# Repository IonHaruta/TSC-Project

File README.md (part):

# TSC - Project

## Diagrama bloc
Diagrama bloc a proiectului nostru prezintă conexiunile dintre senzorii folosiți, microcontrollerul ESP32-C6 și componentele auxiliare:

 <!-- imaginea se pune în folderul proiectului -->

## Prezentare generală

Acest proiect TSC constă într-un sistem integrat care monitorizează temperatura și umiditatea mediului înconjurător cu ajutorul unui senzor DHT22 și afișează datele în timp real pe un ecran OLED SSD1306. Controlul și logica sistemului sunt gestionate de microcontrollerul ESP32-C6, iar interacțiunea utilizatorului se face printr-un buton fizic. Toate componentele sunt alimentate prin USB și sunt integrate pe o placă PCB proiectată în Fusion 360.

## BOM (Bill Of Materials)

| Component       | Device                | Link                                                                 | Datasheet                                                                 |
|-----------------|-----------------------|----------------------------------------------------------------------|---------------------------------------------------------------------------|
| BOOT_BUTTON     | BUTTON_CUSYOMV1        | [Link](https://ro.mouser.com/ProductDetail/Panasonic/EVQ-P7L01P?qs=rJ%252BziJWpyszWhhNszc02jQ%3D%3D&_gl=1*xzqk3l*_ga*dW5kZWZpbmVk*_ga_15W4STQT4T*dW5kZWZpbmVk*_ga_1KQLCYKRX3*dW5kZWZpbmVk)     | [Datasheet](https://componentsearchengine.com/Datasheets/2/EVQP7L01P.pdf) |
| C1              | ESP32_WROVER_EAGLE-LTSPICE_CC0402 | [Link](https://ro.mouser.com/ProductDetail/YAGEO/CC0402MRX5R5BB106?qs=zEY9bCHj09eCmUJdZuS5Lg%3D%3D)  | [Datasheet](https://componentsearchengine.com/Datasheets/2/CC0402MRX5R5BB106.pdf) |
| C1_BAT          | ESP32_WROVER_EAGLE-LTSPICE_CC0402 | [Link](https://ro.mouser.com/ProductDetail/YAGEO/CC0402MRX5R5BB106?qs=zEY9bCHj09eCmUJdZuS5Lg%3D%3D)  | [Datasheet](https://componentsearchengine.com/Datasheets/2/CC0402MRX5R5BB106.pdf) |
| C1_BAT1         | EAGLE-LTSPICE_CC0402   | [Link](https://ro.mouser.com/ProductDetail/YAGEO/CC0402MRX5R5BB106?qs=zEY9bCHj09eCmUJdZuS5Lg%3D%3D)  | [Datasheet](https://componentsearchengine.com/Datasheets/2/CC0402MRX5R5BB106.pdf) |
| C1_BAT2         | EAGLE-LTSPICE_CC0402   | [Link](https://ro.mouser.com/ProductDetail/YAGEO/CC0402MRX5R5BB106?qs=zEY9bCHj09eCmUJdZuS5Lg%3D%3D)  | [Datasheet](https://componentsearchengine.com/Datasheets/2/CC0402MRX5R5BB106.pdf) |
| C2              | ESP32_WROVER_EAGLE-LTSPICE_CC0402 | [Link](https://ro.mouser.com/ProductDetail/YAGEO/CC0402MRX5R5BB106?qs=zEY9bCHj09eCmUJdZuS5Lg%3D%3D)  | [Datasheet](https://componentsearchengine.com/Datasheets/2/CC0402MRX5R5BB106.pdf) |
| C2_BAT          | ESP32_WROVER_EAGLE-LTSPICE_CC0402 | [Link](https://ro.mouser.com/ProductDetail/YAGEO/CC0402MRX5R5BB106?qs=zEY9bCHj09eCmUJdZuS5Lg%3D%3D)  | [Datasheet](https://componentsearchengine.com/Datasheets/2/CC0402MRX5R5BB106.pdf) |
| C3              | RCL_CPOL-EUCT3528      | [Link](https://ro.mouser.com/ProductDetail/YAGEO/CC0402MRX5R5BB106?qs=zEY9bCHj09eCmUJdZuS5Lg%3D%3D)  | [Datasheet](https://componentsearchengine.com/Datasheets/2/CC0402MRX5R5BB106.pdf) |
| C4              | ESP32_WROVER_EAGLE-LTSPICE_CC0402 | [Link](https://ro.mouser.com/ProductDetail/YAGEO/CC0402MRX5R5BB106?qs=zEY9bCHj09eCmUJdZuS5Lg%3D%3D)  | [Datasheet](https://componentsearchengine.com/Datasheets/2/CC0402MRX5R5BB106.pdf) |
| C4_USB          | ESP32_WROVER_EAGLE-LTSPICE_CC0402 | [Link](https://ro.mouser.com/ProductDetail/YAGEO/CC0402MRX5R5BB106?qs=zEY9bCHj09eCmUJdZuS5Lg%3D%3D)  | [Datasheet](https://componentsearchengine.com/Datasheets/2/CC0402MRX5R5BB106.pdf) |
| C5              | ESP32_WROVER_EAGLE-LTSPICE_CC0402 | [Link](https://ro.mouser.com/ProductDetail/YAGEO/CC0402MRX5R5BB106?qs=zEY9bCHj09eCmUJdZuS5Lg%3D%3D)  | [Datasheet](https://componentsearchengine.com/Datasheets/2/CC0402MRX5R5BB106.pdf) |
| C5_USB          | ESP32_WROVER_EAGLE-LTSPICE_CC0402 | [Link](https://ro.mouser.com/ProductDetail/YAGEO/CC0402MRX5R5BB106?qs=zEY9bCHj09eCmUJdZuS5Lg%3D%3D)  | [Datasheet](https://componentsearchengine.com/Datasheets/2/CC0402MRX5R5BB106.pdf) |
| C6              | ESP32_WROVER_EAGLE-LTSPICE_CC0402 | [Link](https://ro.mouser.com/ProductDetail/YAGEO/CC0402MRX5R5BB106?qs=zEY9bCHj09eCmUJdZuS5Lg%3D%3D)  | [Datasheet](https://componentsearchengine.com/Datasheets/2/CC0402MRX5R5BB106.pdf) |
| C7              | ESP32_WROVER_EAGLE-LTSPICE_CC0402 | [Link](https://ro.mouser.com/ProductDetail/YAGEO/CC0402MRX5R5BB106?qs=zEY9bCHj09eCmUJdZuS5Lg%3D%3D)  | [Datasheet](https://componentsearchengine.com/Datasheets/2/CC0402MRX5R5BB106.pdf) |
| C8              | ESP32_WROVER_EAGLE-LTSPICE_CC0402 | [Link](https://ro.mouser.com/ProductDetail/YAGEO/CC0402MRX5R5BB106?qs=zEY9bCHj09eCmUJdZuS5Lg%3D%3D)  | [Datasheet](https://componentsearchengine.com/Datasheets/2/CC0402MRX5R5BB106.pdf) |
| C9              | EAGLE-LTSPICE_CC0402   | [Link](https://ro.mouser.com/ProductDetail/YAGEO/CC0402MRX5R5BB106?qs=zEY9bCHj09eCmUJdZuS5Lg%3D%3D)  | [Datasheet](https://componentsearchengine.com/Datasheets/2/CC0402MRX5R5BB106.pdf) |
| C10             | ESP32_WROVER_EAGLE-LTSPICE_CC0402 | [Link](https://ro.mouser.com/ProductDetail/YAGEO/CC0402MRX5R5BB106?qs=zEY9bCHj09eCmUJdZuS5Lg%3D%3D)  | [Datasheet](https://componentsearchengine.com/Datasheets/2/CC0402MRX5R5BB106.pdf) |
| C10_SUPERCAP    | CPH3225A               | [Link](https://ro.mouser.com/ProductDetail/Seiko-Semiconductors/CPH3225A?qs=3etwrb1wR%252BhUOph6lAO7eg%3D%3D) | [Datasheet](https://ro.mouser.com/datasheet/2/360/Seiko_Instruments_MicroBattery_E_20230330_2024Jan_-3561061.pdf) |
| CHANGE_BUTTON   | BUTTON_CUSYOMV1        | [Link](https://ro.mouser.com/ProductDetail/Panasonic/EVQ-P7L01P?qs=rJ%252BziJWpyszWhhNszc02jQ%3D%3D&_gl=1*xzqk3l*_ga*dW5kZWZpbmVk*_ga_15W4STQT4T*dW5kZWZpbmVk*_ga_1KQLCYKRX3*dW5kZWZpbmVk)     | [Datasheet](https://componentsearchengine.com/Datasheets/2/EVQP7L01P.pdf) |
| C_DELAY         | ESP32_WROVER_EAGLE-LTSPICE_CC0402 | [Link](https://ro.mouser.com/ProductDetail/YAGEO/CC0402MRX5R5BB106?qs=zEY9bCHj09eCmUJdZuS5Lg%3D%3D)  | [Datasheet](https://componentsearchengine.com/Datasheets/2/CC0402MRX5R5BB106.pdf) |
| D1              | USBLC6-2SC6Y           | [Link](https://ro.mouser.com/ProductDetail/STMicroelectronics/USBLC6-2SC6Y?qs=gNDSiZmRJS%2FOgDexvXkdow%3D%3D) | [Datasheet](https://ro.mouser.com/datasheet/2/389/usblc6_2sc6y-1852505.pdf) |
| D2              | ESP32_WROVER_AVX...SD0805S020S1R0_AVX_... | [Link](https://eu.mouser.com/ProductDetail/KYOCERA-AVX/SD0805S020S1R0?qs=jCA%252BPfw4LHbpkAoSnwrdjw%3D%3D) | [Datasheet](http://datasheets.avx.com/schottky.pdf) |
| D3              | MBR0530               | [Link](https://www.snapeda.com/parts/MBR0530/Onsemi/view-part/?ref=eda) | [Datasheet](https://www.snapeda.com/parts/MBR0530/Onsemi/view-part/?ref=eda) |
| D4              | MBR0530               | [Link](https://www.snapeda.com/parts/MBR0530/Onsemi/view-part/?ref=eda) | [Datasheet](https://www.snapeda.com/parts/MBR0530/Onsemi/view-part/?ref=eda) |
| D5              | MBR0530               | [Link](https://www.snapeda.com/parts/MBR0530/Onsemi/view-part/?ref=eda) | [Datasheet](https://www.snapeda.com/parts/MBR0530/Onsemi/view-part/?ref=eda) |
| D6              | PGB1010603MR          | [Link](https://www.snapeda.com/parts/PGB1010603MR/Littelfuse/view-part/?ref=eda) | [Datasheet](https://www.snapeda.com/parts/PGB1010603MR/Littelfuse/view-part/?ref=eda) |
| D7              | ESP32_WROVER_AVX---SD0805S020S1R0_AVX_... | [Link](https://eu.mouser.com/ProductDetail/KYOCERA-AVX/SD0805S020S1R0?qs=jCA%252BPfw4LHbpkAoSnwrdjw%3D%3D) | [Datasheet](http://datasheets.avx.com/schottky.pdf) |
| D8              | PGB1010603MR          | [Link](https://www.snapeda.com/parts/PGB1010603MR/Littelfuse/view-part/?ref=eda) | [Datasheet](https://www.snapeda.com/parts/PGB1010603MR/Littelfuse/view-part/?ref=eda) |
| D9              | PGB1010603MR          | [Link](https://www.snapeda.com/parts/PGB1010603MR/Littelfuse/view-part/?ref=eda) | [Datasheet](https://www.snapeda.com/parts/PGB1010603MR/Littelfuse/view-part/?ref=eda) |
| D10             | PGB1010603MR          | [Link](https://www.snapeda.com/parts/PGB1010603MR/Littelfuse/view-part/?ref=eda) | [Datasheet](https://www.snapeda.com/parts/PGB1010603MR/Littelfuse/view-part/?ref=eda) |
| D11             | PGB1010603MR          | [Link](https://www.snapeda.com/parts/PGB1010603MR/Littelfuse/view-part/?ref=eda) | [Datasheet](https://www.snapeda.com/parts/PGB1010603MR/Littelfuse/view-part/?ref=eda) |
| D12             | PGB1010603MR          | [Link](https://www.snapeda.com/parts/PGB1010603MR/Littelfuse/view-part/?ref=eda) | [Datasheet](https://www.snapeda.com/parts/PGB1010603MR/Littelfuse/view-part/?ref=eda) |
| EPD_C1          | ESP32_WROVER_EAGLE-LTSPICE_CC0402 | [Link](https://ro.mouser.com/ProductDetail/YAGEO/CC0402MRX5R5BB106?qs=zEY9bCHj09eCmUJdZuS5Lg%3D%3D)  | [Datasheet](https://componentsearchengine.com/Datasheets/2/CC0402MRX5R5BB106.pdf) |
| EPD_C2          | ESP32_WROVER_EAGLE-LTSPICE_CC0402 | [Link](https://ro.mouser.com/ProductDetail/YAGEO/CC0402MRX5R5BB106?qs=zEY9bCHj09eCmUJdZuS5Lg%3D%3D)  | [Datasheet](https://componentsearchengine.com/Datasheets/2/CC0402MRX5R5BB106.pdf) |
| EPD_C5          | ESP32_WROVER_EAGLE-LTSPICE_CC0402 | [Link](https://ro.mouser.com/ProductDetail/YAGEO/CC0402MRX5R5BB106?qs=zEY9bCHj09eCmUJdZuS5Lg%3D%3D)  | [Datasheet](https://componentsearchengine.com/Datasheets/2/CC0402MRX5R5BB106.pdf) |
| EPD_C6          | ESP32_WROVER_EAGLE-LTSPICE_CC0402 | [Link](https://ro.mouser.com/ProductDetail/YAGEO/CC0402MRX5R5BB106?qs=zEY9bCHj09eCmUJdZuS5Lg%3D%3D)  | [Datasheet](https://componentsearchengine.com/Datasheets/2/CC0402MRX5R5BB106.pdf) |
| EPD_C7          | ESP32_WROVER_EAGLE-LTSPICE_CC0402 | [Link](https://ro.mouser.com/ProductDetail/YAGEO/CC0402MRX5R5BB106?qs=zEY9bCHj09eCmUJdZuS5Lg%3D%3D)  | [Datasheet](https://componentsearchengine.com/Datasheets/2/CC0402MRX5R5BB106.pdf) |
| EPD_C8          | ESP32_WROVER_EAGLE-LTSPICE_CC0402 | [Link](https://ro.mouser.com/ProductDetail/YAGEO/CC0402MRX5R5BB106?qs=zEY9bCHj09eCmUJdZuS5Lg%3D%3D)  | [Datasheet](https://componentsearchengine.com/Datasheets/2/CC0402MRX5R5BB106.pdf) |
| EPD_C9          | ESP32_WROVER_EAGLE-LTSPICE_CC0402 | [Link](https://ro.mouser.com/ProductDetail/YAGEO/CC0402MRX5R5BB106?qs=zEY9bCHj09eCmUJdZuS5Lg%3D%3D)  | [Datasheet](https://componentsearchengine.com/Datasheets/2/CC0402MRX5R5BB106.pdf) |
| EPD_C10         | ESP32_WROVER_EAGLE-LTSPICE_CC0402 | [Link](https://ro.mouser.com/ProductDetail/YAGEO/CC0402MRX5R5BB106?qs=zEY9bCHj09eCmUJdZuS5Lg%3D%3D)  | [Datasheet](https://componentsearchengine.com/Datasheets/2/CC0402MRX5R5BB106.pdf) |
| EPD_C11         | ESP32_WROVER_EAGLE-LTSPICE_CC0402 | [Link](https://ro.mouser.com/ProductDetail/YAGEO/CC0402MRX5R5BB106?qs=zEY9bCHj09eCmUJdZuS5Lg%3D%3D)  | [Datasheet](https://componentsearchengine.com/Datasheets/2/CC0402MRX5R5BB106.pdf) |
| EPD_C12         | ESP32_WROVER_EAGLE-LTSPICE_CC0402 | [Link](https://ro.mouser.com/ProductDetail/YAGEO/CC0402MRX5R5BB106?qs=zEY9bCHj09eCmUJdZuS5Lg%3D%3D)  | [Datasheet](https://componentsearchengine.com/Datasheets/2/CC0402MRX5R5BB106.pdf) |
| IC1             | BD5229G-TR            | [Link](https://ro.mouser.com/ProductDetail/ROHM-Semiconductor/BD5229G-TR?qs=4kLU8WoGk0vvnhrrYwdszw%3D%3D) | [Datasheet](https://fscdn.rohm.com/en/products/databook/datasheet/ic/power/voltage_detector/bd52xxg-e.pdf) |
| IC4             | XC6220A331MR-G        | [Link](https://ro.mouser.com/ProductDetail/Torex-Semiconductor/XC6220A331MR-G?qs=AsjdqWjXhJ8ZSWznL1J0gg%3D%3D) | [Datasheet](https://ro.mouser.com/datasheet/2/760/xc6220-3371556.pdf) |
| J1              | FH34SRJ-24S-0.5SH_99_ | [Link](https://ro.mouser.com/ProductDetail/Hirose-Connector/FH34SRJ-24S-0.5SH99?qs=vcbW%252B4%252BSTIpKBl5ap9J8Fw%3D%3D) | [Datasheet](https://ro.mouser.com/datasheet/2/185/FH34SRJ_24S_0_5SH_99__CL0580_1255_6_99_2DDrawing_0-1615044.pdf) |
| J2              | USB4110-GF-A          | [Link](https://ro.mouser.com/ProductDetail/GCT/USB4110-GF-A?qs=KUoIvG%2F9IlYiZvIXQjyJeA%3D%3D) | [Datasheet](https://ro.mouser.com/datasheet/2/837/GCT_USB4110_Product_Drawing___20k_cycles-3455479.pdf) |
| J3              | QWIIC_CONNECTORJS-1MM | [Link](https://ro.mouser.com/ProductDetail/SparkFun/PRT-14417?qs=wd5RIQLrsJhgdz%2FpmZ%2F3GQ%3D%3D) | [Datasheet](https://ro.mouser.com/datasheet/2/813/Qwiic_Connector_Datasheet-1223982.pdf) |
| J4              | 112A-TAAR-R03_ATTEND  | [Link](https://store.comet.srl.ro/Catalogue/Product/43497/) | [Datasheet](https://store.comet.srl.ro/Catalogue/Product/43497/) |
| L1              | 744043680IND_4828-WE-TPC_WRE | [Link](https://ro.mouser.com/ProductDetail/Wurth-Elektronik/744043680?qs=PGXP4M47uW6VkZq%252BkzjrHA%3D%3D) | [Datasheet](https://eu.mouser.com/ProductDetail/Wurth-Elektronik/744043680?qs=PGXP4M47uW6VkZq%252BkzjrHA%3D%3D) |
| PFMF.050.1      | ESP32C6_VARISTORCN1812 | [Link](https://ro.mouser.com/ProductDetail/KEMET/VE1812K401R050?qs=OycAS1CGnlizCtaoDVbQTA%3D%3D) | [Datasheet](https://www.mouser.co.uk/ProductDetail/EPCOS-TDK/B72520T0350K062?qs=dEfas%2FXlABIszF52uu7vrg%3D%3D) |
| Q1              | DMG2305UX-7           | [Link](https://ro.mouser.com/ProductDetail/Diodes-Incorporated/DMG2305UX-7?qs=L1DZKBg7t5F%2FNBHrjfxC%252Bg%3D%3D) | [Datasheet](https://www.diodes.com/assets/Datasheets/DMG2305UX.pdf) |
| Q2              | ESP32_WROVER_SPARKFUN-DISCRETESEMI_MOSFET_... | [Link](https://ro.mouser.com/ProductDetail/Diodes-Incorporated/DMG2305UX-7?qs=L1DZKBg7t5F%2FNBHrjfxC%252Bg%3D%3D) | [Datasheet](https://www.diodes.com/assets/Datasheets/DMG2305UX.pdf) |
| Q3              | D8                    | [Link](https://ro.mouser.com/ProductDetail/Vishay-Semiconductors/SI1308EDL-T1-GE3?qs=bX1%252BNvsK%2FBramh9tgpOaEw%3D%3D) | [Datasheet](https://componentsearchengine.com/part-view/SI1308EDL-T1-GE3/Vishay) |
| R1              | ESP32_WROVER_EAGLE-LTSPICE_RR0402 | [Link](https://ro.mouser.com/ProductDetail/YAGEO/RC0402FR-07100KL?qs=mnq%2FyloZIXzTlUn7JAHSWg%3D%3D) | [Datasheet](https://ro.mouser.com/datasheet/2/447/YAGEO_PYu_RC_Group_51_RoHS_L_12-3313492.pdf) |
| R1_PINH         | ESP32_WROVER_EAGLE-LTSPICE_RR0402 | [Link](https://ro.mouser.com/ProductDetail/YAGEO/RC0402FR-07100KL?qs=mnq%2FyloZIXzTlUn7JAHSWg%3D%3D) | [Datasheet](https://ro.mouser.com/datasheet/2/447/YAGEO_PYu_RC_Group_51_RoHS_L_12-3313492.pdf) |
| R1_PINH1        | ESP32_WROVER_EAGLE-LTSPICE_RR0402 | [Link](https://ro.mouser.com/ProductDetail/YAGEO/RC0402FR-07100KL?qs=mnq%2FyloZIXzTlUn7JAHSWg%3D%3D) | [Datasheet](https://ro.mouser.com/datasheet/2/447/YAGEO_PYu_RC_Group_51_RoHS_L_12-3313492.pdf) |
| R1_BAT          | ESP32_WROVER_EAGLE-LTSPICE_RR0402 | [Link](https://ro.mouser.com/ProductDetail/YAGEO/RC0402FR-07100KL?qs=mnq%2FyloZIXzTlUn7JAHSWg%3D%3D) | [Datasheet](https://ro.mouser.com/datasheet/2/447/YAGEO_PYu_RC_Group_51_RoHS_L_12-3313492.pdf) |
| R1_PWRUSB       | ESP32_WROVER_EAGLE-LTSPICE_RR0402 | [Link](https://ro.mouser.com/ProductDetail/YAGEO/RC0402FR-07100KL?qs=mnq%2FyloZIXzTlUn7JAHSWg%3D%3D) | [Datasheet](https://ro.mouser.com/datasheet/2/447/YAGEO_PYu_RC_Group_51_RoHS_L_12-3313492.pdf) |
| R2              | ESP32_WROVER_EAGLE-LTSPICE_RR0402 | [Link](https://ro.mouser.com/ProductDetail/YAGEO/RC0402FR-07100KL?qs=mnq%2FyloZIXzTlUn7JAHSWg%3D%3D) | [Datasheet](https://ro.mouser.com/datasheet/2/447/YAGEO_PYu_RC_Group_51_RoHS_L_12-3313492.pdf) |
| R2_PINH         | ESP32_WROVER_EAGLE-LTSPICE_RR0402 | [Link](https://ro.mouser.com/ProductDetail/YAGEO/RC0402FR-07100KL?qs=mnq%2FyloZIXzTlUn7JAHSWg%3D%3D) | [Datasheet](https://ro.mouser.com/datasheet/2/447/YAGEO_PYu_RC_Group_51_RoHS_L_12-3313492.pdf) |
| R2_PINH1        | ESP32_WROVER_EAGLE-LTSPICE_RR0402 | [Link](https://ro.mouser.com/ProductDetail/YAGEO/RC0402FR-07100KL?qs=mnq%2FyloZIXzTlUn7JAHSWg%3D%3D) | [Datasheet](https://ro.mouser.com/datasheet/2/447/YAGEO_PYu_RC_Group_51_RoHS_L_12-3313492.pdf) |
| R2_USB          | ESP32_WROVER_EAGLE-LTSPICE_RR0402 | [Link](https://ro.mouser.com/ProductDetail/YAGEO/RC0402FR-07100KL?qs=mnq%2FyloZIXzTlUn7JAHSWg%3D%3D) | [Datasheet](https://ro.mouser.com/datasheet/2/447/YAGEO_PYu_RC_Group_51_RoHS_L_12-3313492.pdf) |
| R2_USB1         | ESP32_WROVER_EAGLE-LTSPICE_RR0402 | [Link](https://ro.mouser.com/ProductDetail/YAGEO/RC0402FR-07100KL?qs=mnq%2FyloZIXzTlUn7JAHSWg%3D%3D) | [Datasheet](https://ro.mouser.com/datasheet/2/447/YAGEO_PYu_RC_Group_51_RoHS_L_12-3313492.pdf) |
| R2_BAT          | ESP32_WROVER_EAGLE-LTSPICE_RR0402 | [Link](https://ro.mouser.com/ProductDetail/YAGEO/RC0402FR-07100KL?qs=mnq%2FyloZIXzTlUn7JAHSWg%3D%3D) | [Datasheet](https://ro.mouser.com/datasheet/2/447/YAGEO_PYu_RC_Group_51_RoHS_L_12-3313492.pdf) |
| R3              | ESP32_WROVER_EAGLE-LTSPICE_RR0402 | [Link](https://ro.mouser.com/ProductDetail/YAGEO/RC0402FR-07100KL?qs=mnq%2FyloZIXzTlUn7JAHSWg%3D%3D) | [Datasheet](https://ro.mouser.com/datasheet/2/447/YAGEO_PYu_RC_Group_51_RoHS_L_12-3313492.pdf) |
| R4              | ESP32_WROVER_EAGLE-LTSPICE_RR0402 | [Link](https://ro.mouser.com/ProductDetail/YAGEO/RC0402FR-07100KL?qs=mnq%2FyloZIXzTlUn7JAHSWg%3D%3D) | [Datasheet](https://ro.mouser.com/datasheet/2/447/YAGEO_PYu_RC_Group_51_RoHS_L_12-3313492.pdf) |
| R5              | ESP32_WROVER_EAGLE-LTSPICE_RR0402 | [Link](https://ro.mouser.com/ProductDetail/YAGEO/RC0402FR-07100KL?qs=mnq%2FyloZIXzTlUn7JAHSWg%3D%3D) | [Datasheet](https://ro.mouser.com/datasheet/2/447/YAGEO_PYu_RC_Group_51_RoHS_L_12-3313492.pdf) |
| R6              | ESP32_WROVER_EAGLE-LTSPICE_RR0402 | [Link](https://ro.mouser.com/ProductDetail/YAGEO/RC0402FR-07100KL?qs=mnq%2FyloZIXzTlUn7JAHSWg%3D%3D) | [Datasheet](https://ro.mouser.com/datasheet/2/447/YAGEO_PYu_RC_Group_51_RoHS_L_12-3313492.pdf) |
| R7              | ESP32_WROVER_EAGLE-LTSPICE_RR0402 | [Link](https://ro.mouser.com/ProductDetail/YAGEO/RC0402FR-07100KL?qs=mnq%2FyloZIXzTlUn7JAHSWg%3D%3D) | [Datasheet](https://ro.mouser.com/datasheet/2/447/YAGEO_PYu_RC_Group_51_RoHS_L_12-3313492.pdf) |
| R8              | ESP32_WROVER_EAGLE-LTSPICE_RR0402 | [Link](https://ro.mouser.com/ProductDetail/YAGEO/RC0402FR-07100KL?qs=mnq%2FyloZIXzTlUn7JAHSWg%3D%3D) | [Datasheet](https://ro.mouser.com/datasheet/2/447/YAGEO_PYu_RC_Group_51_RoHS_L_12-3313492.pdf) |
| R9              | ESP32_WROVER_EAGLE-LTSPICE_RR0402 | [Link](https://ro.mouser.com/ProductDetail/YAGEO/RC0402FR-07100KL?qs=mnq%2FyloZIXzTlUn7JAHSWg%3D%3D) | [Datasheet](https://ro.mouser.com/datasheet/2/447/YAGEO_PYu_RC_Group_51_RoHS_L_12-3313492.pdf) |
| R10             | ESP32_WROVER_EAGLE-LTSPICE_RR0402 | [Link](https://ro.mouser.com/ProductDetail/YAGEO/RC0402FR-07100KL?qs=mnq%2FyloZIXzTlUn7JAHSWg%3D%3D) | [Datasheet](https://ro.mouser.com/datasheet/2/447/YAGEO_PYu_RC_Group_51_RoHS_L_12-3313492.pdf) |
| RESET_BUTTON    | BUTTON_CUSYOMV1        | [Link](https://ro.mouser.com/ProductDetail/Panasonic/EVQ-P7L01P?qs=rJ%252BziJWpyszWhhNszc02jQ%3D%3D&_gl=1*xzqk3l*_ga*dW5kZWZpbmVk*_ga_15W4STQT4T*dW5kZWZpbmVk*_ga_1KQLCYKRX3*dW5kZWZpbmVk)     | [Datasheet](https://componentsearchengine.com/Datasheets/2/EVQP7L01P.pdf) |
| R_BOOT          | ESP32_WROVER_EAGLE-LTSPICE_RR0402 | [Link](https://ro.mouser.com/ProductDetail/YAGEO/RC0402FR-07100KL?qs=mnq%2FyloZIXzTlUn7JAHSWg%3D%3D) | [Datasheet](https://ro.mouser.com/datasheet/2/447/YAGEO_PYu_RC_Group_51_RoHS_L_12-3313492.pdf) |
| R_CAPACITOR     | ESP32_WROVER_EAGLE-LTSPICE_RR0402 | [Link](https://ro.mouser.com/ProductDetail/YAGEO/RC0402FR-07100KL?qs=mnq%2FyloZIXzTlUn7JAHSWg%3D%3D) | [Datasheet](https://ro.mouser.com/datasheet/2/447/YAGEO_PYu_RC_Group_51_RoHS_L_12-3313492.pdf) |
| R_CHANGE        | ESP32_WROVER_EAGLE-LTSPICE_RR0402 | [Link](https://ro.mouser.com/ProductDetail/YAGEO/RC0402FR-07100KL?qs=mnq%2FyloZIXzTlUn7JAHSWg%3D%3D) | [Datasheet](https://ro.mouser.com/datasheet/2/447/YAGEO_PYu_RC_Group_51_RoHS_L_12-3313492.pdf) |
| R_CL1           | ESP32_WROVER_EAGLE-LTSPICE_RR0402 | [Link](https://ro.mouser.com/ProductDetail/YAGEO/RC0402FR-07100KL?qs=mnq%2FyloZIXzTlUn7JAHSWg%3D%3D) | [Datasheet](https://ro.mouser.com/datasheet/2/447/YAGEO_PYu_RC_Group_51_RoHS_L_12-3313492.pdf) |
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
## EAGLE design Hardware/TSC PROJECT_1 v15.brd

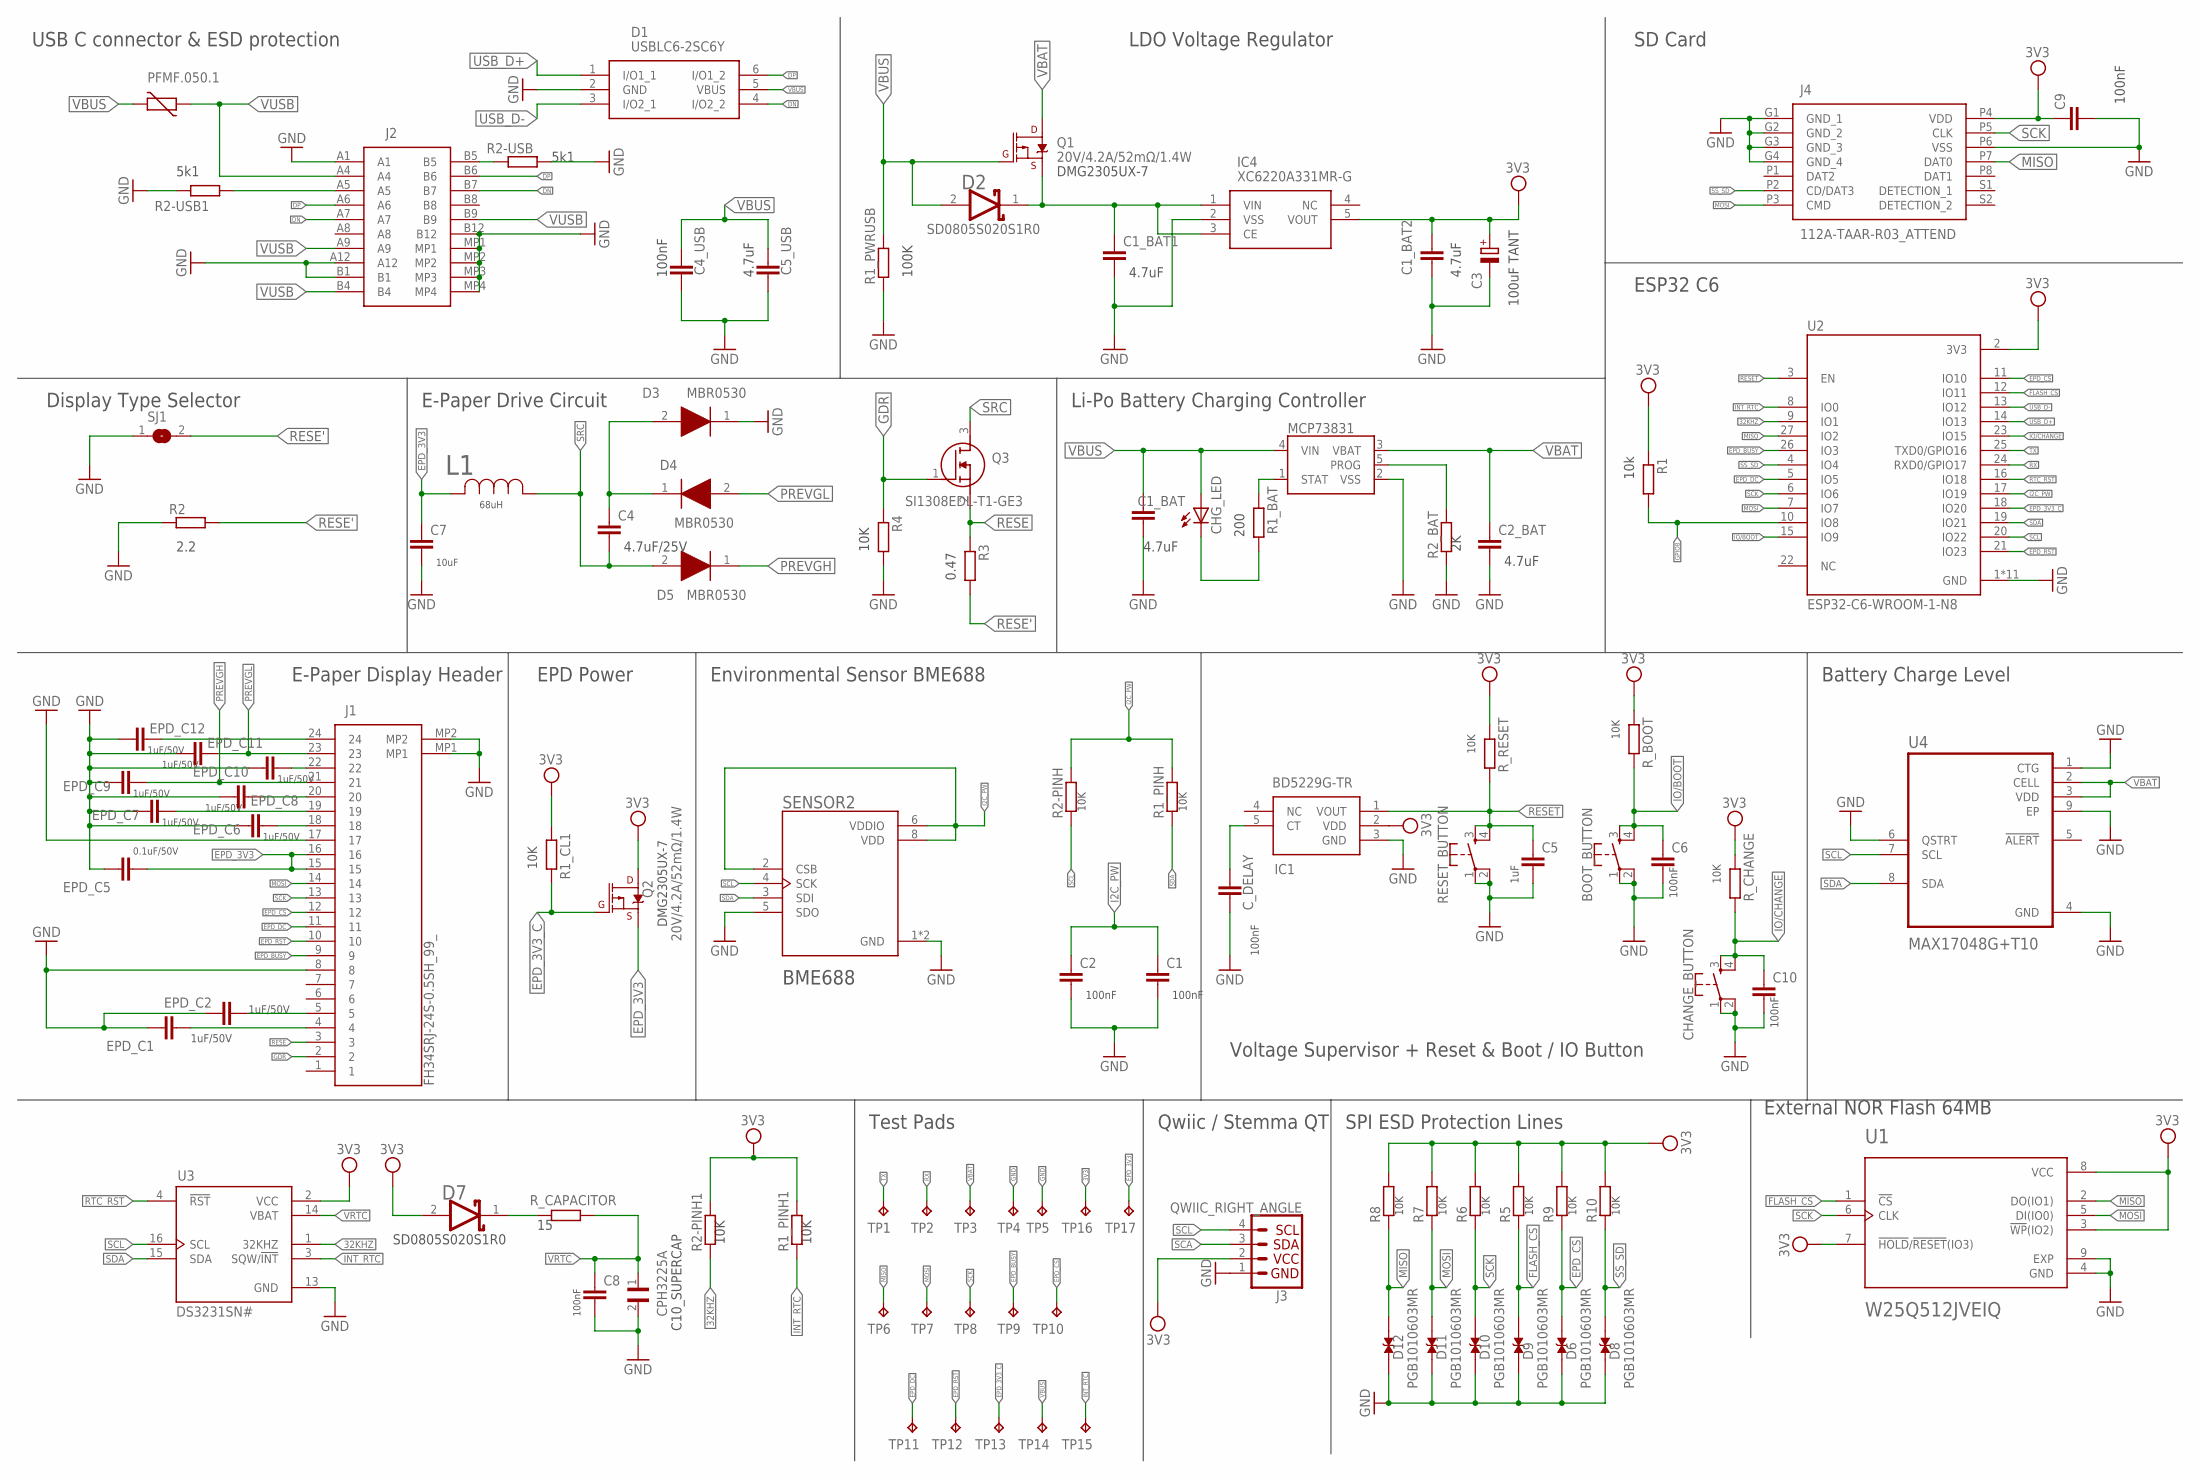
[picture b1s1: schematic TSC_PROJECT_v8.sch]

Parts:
BOOT_BUTTON: BUTTON_CUSYOMV1; MYBUTTON
C1, C1_BAT, C1_BAT1, C1_BAT2, C2, C2_BAT, C4, C4_USB, C5, C5_USB, C6, C7, C8, C9, C10: EAGLE-LTSPICE_CC0402; EAGLE-LTSPICE_C0402
C3: RCL_CPOL-EUCT3528; RCL_CT3528
CHANGE_BUTTON: BUTTON_CUSYOMV1; MYBUTTON
CHG_LED: ADAFRUIT_LEDCHIP-LED0603; ADAFRUIT_CHIP-LED0603
CPH3225A: CPH3225A; CAPCP3225X100N
C_DELAY: EAGLE-LTSPICE_CC0402; EAGLE-LTSPICE_C0402
D1: USBLC6-2SC6Y; SOT95P280X145-6N
D2, D7: ESP32_WROVER_AVX---SD0805S020S1R0_AVX_SD0805S020S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; ESP32_WROVER_AVX---SD0805S020S1R0_AVX_SD0805S020S1R0_0
D3, D4, D5: MBR0530; SOD3716X135N
D6, D8, D9, D10, D11, D12: PGB1010603MR; DIOC1608X36N
EPD_C1, EPD_C2, EPD_C5, EPD_C6, EPD_C7, EPD_C8, EPD_C9, EPD_C10, EPD_C11, EPD_C12: EAGLE-LTSPICE_CC0402; EAGLE-LTSPICE_C0402
IC1: BD5229G-TR; SOT95P280X125-5N
IC4: XC6220A331MR-G; SOT95P280X120-5N
J1: FH34SRJ-24S-0.5SH_99_; FH34SRJ24S05SH99
J2: SAMACSYS_PARTS_USB4110-GF-A; SAMACSYS_PARTS_USB4110GFA
J3: QWIIC_RIGHT_ANGLE; JST04_1MM_RA
J4: 112A-TAAR-R03_ATTEND; 112ATAARR03ATTEND
L1: 744043680IND_4828-WE-TPC_WRE; IND_4828-WE-TPC_WRE
MCP73831: ESP32_WROVER_SPARKFUN-IC-POWER_MCP73831; ESP32_WROVER_SPARKFUN-IC-POWER_SOT23-5
PFMF.050.1: ESP32C6_VARISTORCN1812; ESP32C6_VARISTOR_CT/CN1812
Q1, Q2: 20V/4.2A/52mΩ/1.4W; ESP32_WROVER_SPARKFUN-DISCRETESEMI_SOT23-3
Q3: SI1308EDL-T1-GE3; SOT65P210X110-3N
R1, R1_BAT, R1_CL1, R1_PINH, R1_PINH1, R1_PWRUSB, R2, R2-PINH, R2-PINH1, R2-USB, R2-USB1, R2_BAT, R3, R4, R5, R6, R7, R8, R9, R10: ESP32_WROVER_EAGLE-LTSPICE_RR0402; ESP32_WROVER_EAGLE-LTSPICE_R0402
RESET_BUTTON: BUTTON_CUSYOMV1; MYBUTTON
R_BOOT: ESP32_WROVER_EAGLE-LTSPICE_RR0402; ESP32_WROVER_EAGLE-LTSPICE_R0402
R_CAPACITOR: ESP32_WROVER_EAGLE-LTSPICE_RR0402; ESP32_WROVER_EAGLE-LTSPICE_R0402
R_CHANGE: ESP32_WROVER_EAGLE-LTSPICE_RR0402; ESP32_WROVER_EAGLE-LTSPICE_R0402
R_RESET: ESP32_WROVER_EAGLE-LTSPICE_RR0402; ESP32_WROVER_EAGLE-LTSPICE_R0402
SENSOR2: ESP32_WROVER_BME680_BME680; ESP32_WROVER_BME680_PSON80P300X300X100-8N
SJ1: SJ
TP1, TP2, TP3, TP4, TP5, TP6, TP7, TP8, TP9, TP10, TP11, TP12, TP13, TP14, TP15, TP16, TP17: TPTP20R; TP20R
U1: W25Q512JVEIQ; SON127P600X800X80-9N
U2: ESP32-C6-WROOM-1-N8; XCVR_ESP32-C6-WROOM-1-N8
U3: DS3231SN#; SOIC127P1032X265-16N
U4: MAX17048G+T10; SON50P200X200X80-9N

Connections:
3V3: C9.1, D7.2 (ANODE), IC1.2 (VDD), J3.2, J4.P4 (VDD), Q2.3 (D), R1.1, R1_CL1.1, R1_PINH1.2, R2-PINH1.2, R5.2, R6.2, R7.2, R8.2, R9.2, R10.2, R_BOOT.1, R_CHANGE.1, R_RESET.1, TP16.TP, U1.3 (!WP!(IO2)), U1.7 (!HOLD!/!RESET!(IO3)), U1.8 (VCC), U2.2 (3V3), U3.2 (VCC)
4.7UF: C1_BAT2.2, C3.-, C4_USB.2, C5_USB.2
32KHZ: R2-PINH1.1, U2.9 (IO1), U3.1 (32KHZ)
100K: R1_PWRUSB.1
100UFTANT: C1_BAT2.1, C3.+, IC4.5 (VOUT)
DN: D1.4 (I/O2_2), J2.A7, J2.B7
DP: D1.6 (I/O1_2), J2.A6, J2.B6
EPD_3V3: C7.1, EPD_C5.1, J1.15, J1.16, L1.2, Q2.2 (S), TP17.TP
EPD_3V3_C: Q2.1 (G), R1_CL1.2, TP13.TP, U2.18 (IO20)
EPD_BUSY: J1.9, TP9.TP, U2.26 (IO3)
EPD_CS: D6.2, J1.12, R9.1, TP10.TP, U2.11 (IO10)
EPD_DC: J1.11, TP11.TP, U2.5 (IO5)
EPD_RST: J1.10, TP12.TP, U2.21 (IO23)
FLASH_CS: D9.2, R5.1, U1.1 (!CS), U2.12 (IO11)
GDR: J1.2, Q3.1 (G), R4.1
GND: BOOT_BUTTON.1, BOOT_BUTTON.2, C1.2, C1_BAT.2, C1_BAT1.2, C2.2, C2_BAT.2, C5.2, C6.2, C7.2, C8.2, C9.2, C10.2, CHANGE_BUTTON.1, CHANGE_BUTTON.2, CPH3225A.2, C_DELAY.2, D1.2 (GND), D3.1 (K), D6.1, D8.1, D9.1, D10.1, D11.1, D12.1, EPD_C1.2, EPD_C2.2, EPD_C5.2, EPD_C6.2, EPD_C7.2, EPD_C8.2, EPD_C9.2, EPD_C10.2, EPD_C11.2, EPD_C12.2, IC1.3 (GND), IC4.2 (VSS), J1.8, J1.17, J1.MP1, J1.MP2, J2.A12, J2.B1, J2.B12, J2.MP1, J2.MP2, J2.MP3, J2.MP4, J3.1, J4.G1 (GND_1), J4.G2 (GND_2), J4.G3 (GND_3), J4.G4 (GND_4), J4.P6 (VSS), MCP73831.2 (VSS), R2.1, R2-USB.2, R2_BAT.1, R4.2, RESET_BUTTON.1, RESET_BUTTON.2, SENSOR2.1 (GND), SENSOR2.5 (SDO), SENSOR2.7 (GND), SJ1.1, TP4.TP, TP5.TP, U1.4 (GND), U1.9 (EXP), U2.1 (GND), U2.28 (GND), U2.29_1 (GND), U2.29_2 (GND), U2.29_3 (GND), U2.29_4 (GND), U2.29_5 (GND), U2.29_6 (GND), U2.29_7 (GND), U2.29_8 (GND), U2.29_9 (GND), U3.13 (GND), U4.1 (CTG), U4.4 (GND), U4.6 (QSTRT), U4.9 (EP)
GPIO8: R1.2, U2.10 (IO8)
I2C_PW: C1.1, C2.1, R1_PINH.2, R2-PINH.2, SENSOR2.2 (CSB), SENSOR2.6 (VDDIO), SENSOR2.8 (VDD), U2.17 (IO19)
INT_RTC: R1_PINH1.1, TP15.TP, U2.8 (IO0), U3.3 (SQW/!INT)
IO/BOOT: BOOT_BUTTON.3, BOOT_BUTTON.4, C6.1, R_BOOT.2, U2.15 (IO9)
IO/CHANGE: C10.1, CHANGE_BUTTON.3, CHANGE_BUTTON.4, R_CHANGE.2, U2.23 (IO15)
MISO: D12.2, J4.P7 (DAT0), R8.1, TP6.TP, U1.2 (DO(IO1)), U2.27 (IO2)
MOSI: D11.2, J1.14, J4.P3 (CMD), R7.1, TP7.TP, U1.5 (DI(IO0)), U2.7 (IO7)
unnamed: J2.A5, R2-USB1.2
unnamed: J2.B5, R2-USB.1
unnamed: C4.1, D3.2 (A), D4.1 (K)
unnamed: MCP73831.1 (STAT), R1_BAT.1
unnamed: CHG_LED.C, R1_BAT.2
unnamed: MCP73831.5 (PROG), R2_BAT.2
unnamed: EPD_C12.1, J1.24
unnamed: EPD_C2.1, J1.5
unnamed: EPD_C10.1, J1.22
unnamed: C_DELAY.1, IC1.5 (CT)
unnamed: EPD_C8.1, J1.20
unnamed: EPD_C7.1, J1.19
unnamed: EPD_C6.1, J1.18
unnamed: EPD_C1.1, J1.4
unnamed: D7.1 (CATHODE), R_CAPACITOR.2
PREVGH: D5.1 (K), EPD_C9.1, J1.21
PREVGL: D4.2 (A), EPD_C11.1, J1.23
R2-USB1: R2-USB1.1
RESE: J1.3, Q3.2 (S), R3.1
RESE': R2.2, R3.2, SJ1.2
RESET: C5.1, IC1.1 (VOUT), RESET_BUTTON.3, RESET_BUTTON.4, R_RESET.2, U2.3 (EN)
RTC_RST: U2.16 (IO18), U3.4 (!RST)
RX: TP2.TP, U2.24 (RXD0/GPIO17)
SCA: J3.3
SCK: D10.2, J1.13, J4.P5 (CLK), R6.1, TP8.TP, U1.6 (CLK), U2.6 (IO6)
SCL: J3.4, R2-PINH.1, SENSOR2.4 (SCK), U2.20 (IO22), U3.16 (SCL), U4.7 (SCL)
SD0805S020S1R0: C1_BAT1.1, D2.1 (CATHODE), IC4.1 (VIN), IC4.3 (CE), Q1.2 (S)
SDA: R1_PINH.1, SENSOR2.3 (SDI), U2.19 (IO21), U3.15 (SDA), U4.8 (SDA)
SRC: C4.2, D5.2 (A), L1.1, Q3.3 (D)
SS_SD: D8.2, J4.P2 (CD/DAT3), R10.1, U2.4 (IO4)
TX: TP1.TP, U2.25 (TXD0/GPIO16)
USB_D+: D1.1 (I/O1_1), U2.14 (IO13)
USB_D-: D1.3 (I/O2_1), U2.13 (IO12)
VBAT: C2_BAT.1, MCP73831.3 (VBAT), Q1.3 (D), TP3.TP, U4.2 (CELL), U4.3 (VDD)
VBUS: C1_BAT.1, C4_USB.1, C5_USB.1, CHG_LED.A, D1.5 (VBUS), D2.2 (ANODE), MCP73831.4 (VIN), PFMF.050.1.2, Q1.1 (G), R1_PWRUSB.2, TP14.TP
VRTC: C8.1, CPH3225A.1, R_CAPACITOR.1, U3.14 (VBAT)
VUSB: J2.A4, J2.A9, J2.B4, J2.B9, PFMF.050.1.1

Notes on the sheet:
USB C connector & ESD protection
DMG2305UX-7
4.7uF
100K
100uF TANT
100nF
5k1
LDO Voltage Regulator
SD Card
2.2
Display Type Selector
10uF
68uH
4.7uF/25V
0.47
10K
E-Paper Drive Circuit
200
Li-Po Battery Charging Controller
10k
ESP32 C6
1uF/50V
0.1uF/50V
E-Paper Display Header
EPD Power
BME688
Environmental Sensor BME688
1uF
Voltage Supervisor + Reset & Boot / IO Button
Battery Charge Level
SD0805S020S1R0
C10_SUPERCAP
Test Pads
Qwiic / Stemma QT
SPI ESD Protection Lines
External NOR Flash 64MB

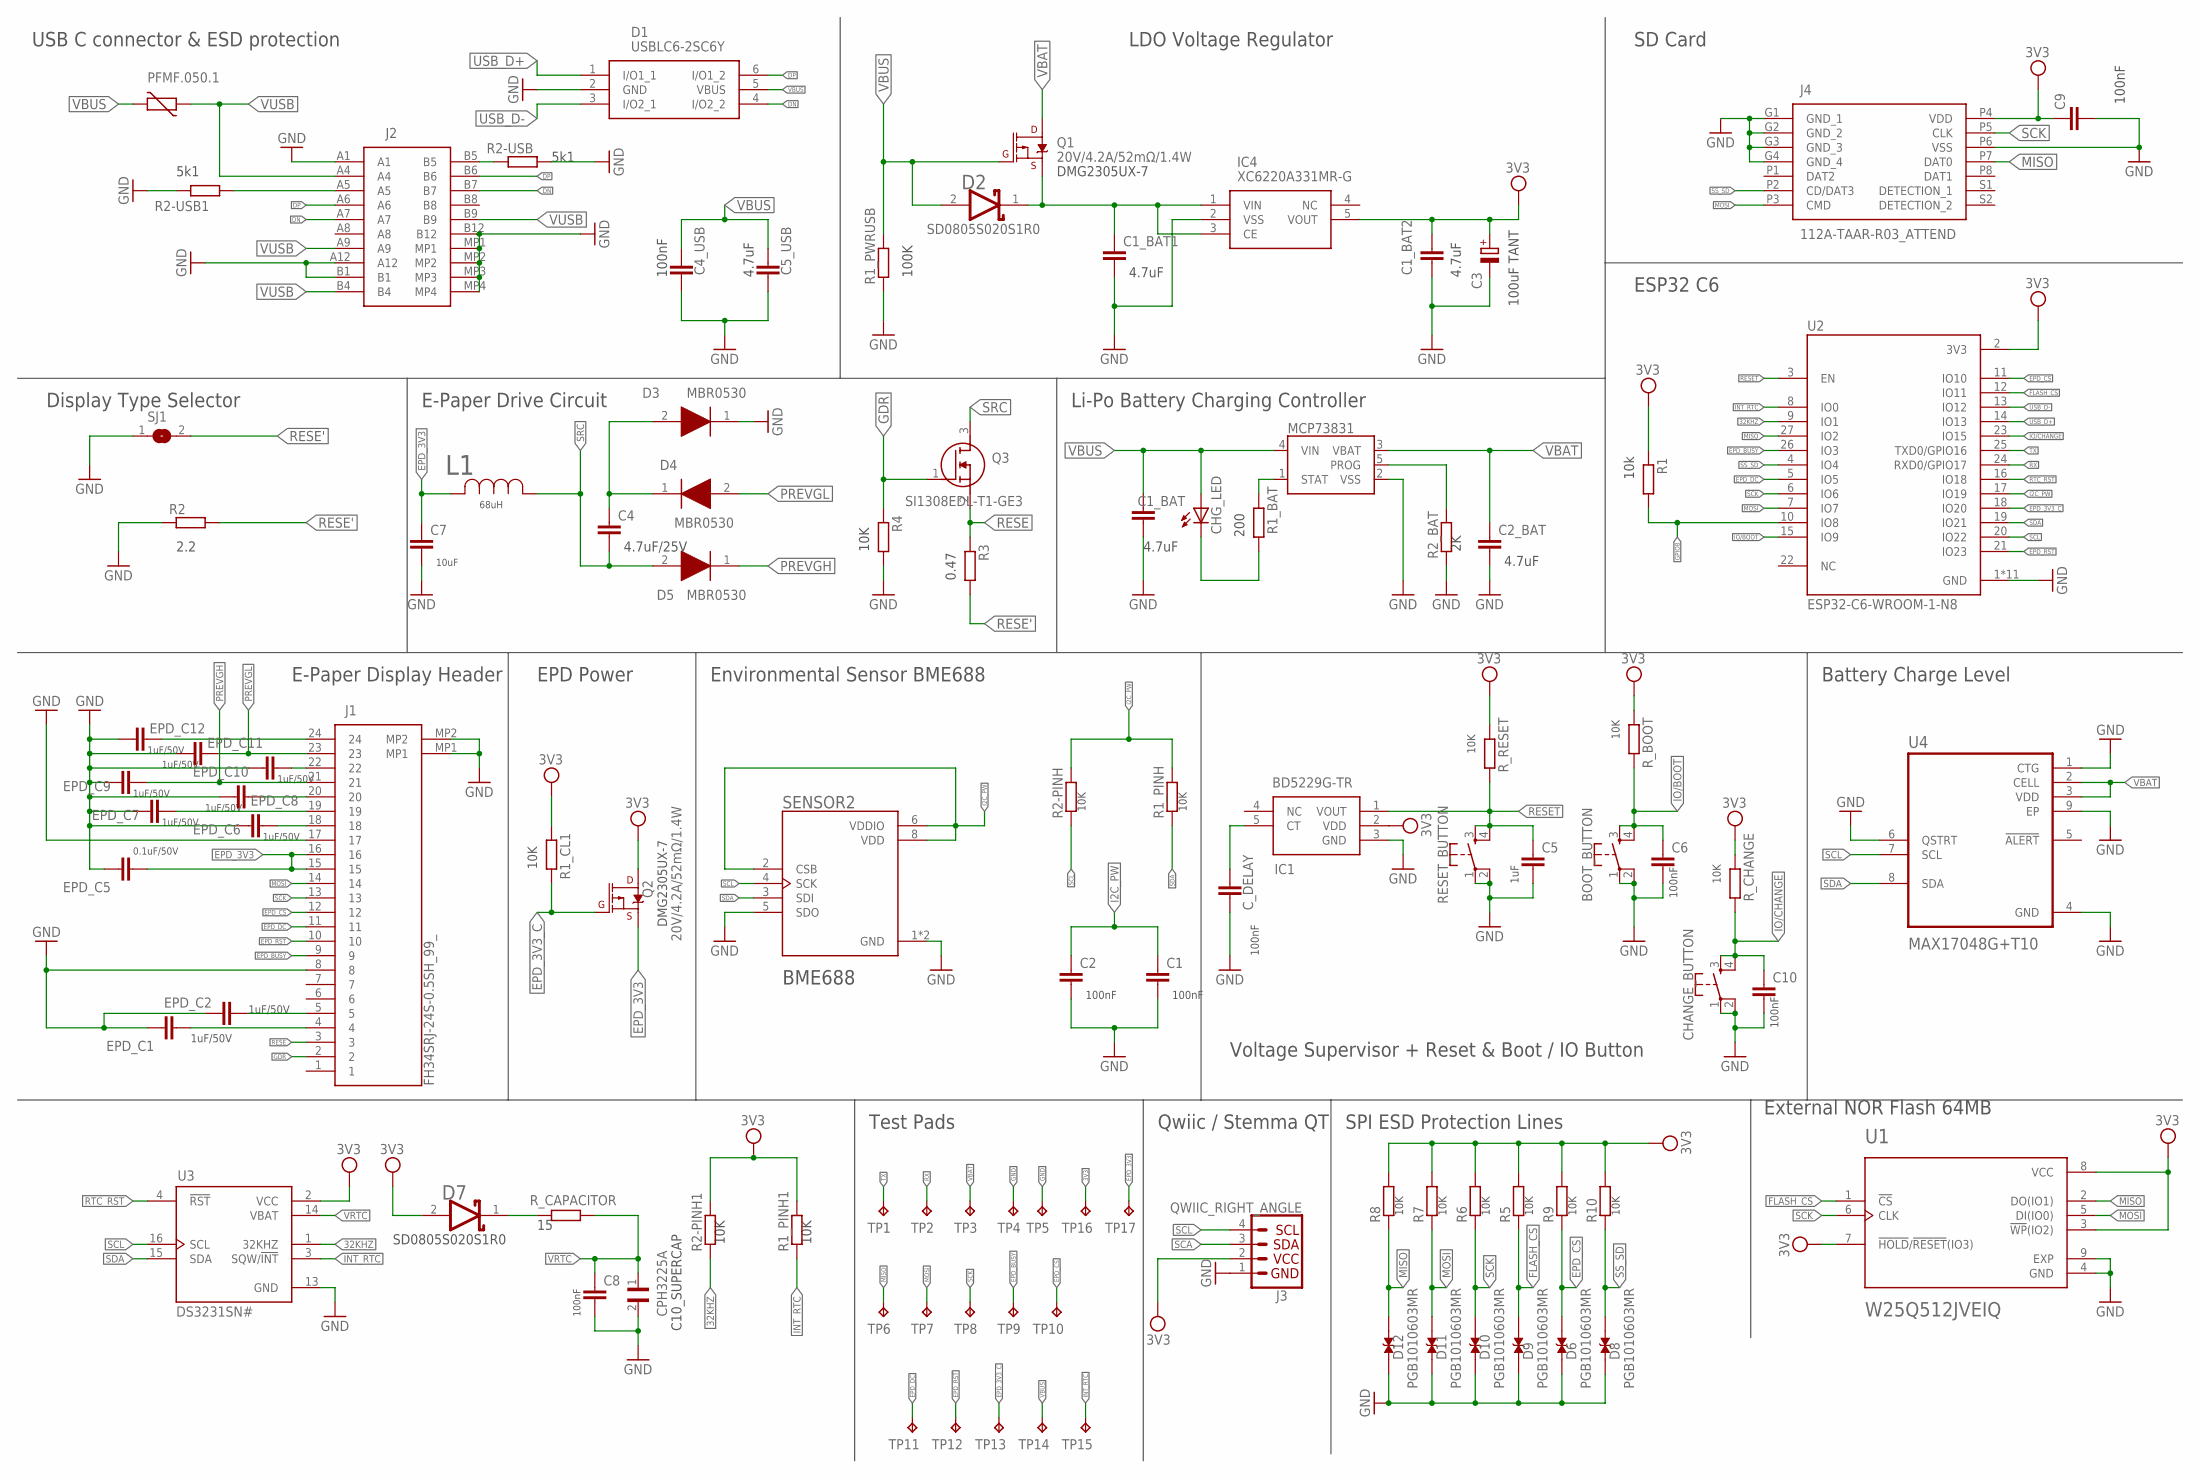
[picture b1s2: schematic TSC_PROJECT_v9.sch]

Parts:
BOOT_BUTTON: BUTTON_CUSYOMV1; MYBUTTON
C1, C1_BAT, C1_BAT1, C1_BAT2, C2, C2_BAT, C4, C4_USB, C5, C5_USB, C6, C7, C8, C9, C10: EAGLE-LTSPICE_CC0402; EAGLE-LTSPICE_C0402
C3: RCL_CPOL-EUCT3528; RCL_CT3528
CHANGE_BUTTON: BUTTON_CUSYOMV1; MYBUTTON
CHG_LED: ADAFRUIT_LEDCHIP-LED0603; ADAFRUIT_CHIP-LED0603
CPH3225A: CPH3225A; CAPCP3225X100N
C_DELAY: EAGLE-LTSPICE_CC0402; EAGLE-LTSPICE_C0402
D1: USBLC6-2SC6Y; SOT95P280X145-6N
D2, D7: ESP32_WROVER_AVX---SD0805S020S1R0_AVX_SD0805S020S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; ESP32_WROVER_AVX---SD0805S020S1R0_AVX_SD0805S020S1R0_0
D3, D4, D5: MBR0530; SOD3716X135N
D6, D8, D9, D10, D11, D12: PGB1010603MR; DIOC1608X36N
EPD_C1, EPD_C2, EPD_C5, EPD_C6, EPD_C7, EPD_C8, EPD_C9, EPD_C10, EPD_C11, EPD_C12: EAGLE-LTSPICE_CC0402; EAGLE-LTSPICE_C0402
IC1: BD5229G-TR; SOT95P280X125-5N
IC4: XC6220A331MR-G; SOT95P280X120-5N
J1: FH34SRJ-24S-0.5SH_99_; FH34SRJ24S05SH99
J2: SAMACSYS_PARTS_USB4110-GF-A; SAMACSYS_PARTS_USB4110GFA
J3: QWIIC_RIGHT_ANGLE; JST04_1MM_RA
J4: 112A-TAAR-R03_ATTEND; 112ATAARR03ATTEND
L1: 744043680IND_4828-WE-TPC_WRE; IND_4828-WE-TPC_WRE
MCP73831: ESP32_WROVER_SPARKFUN-IC-POWER_MCP73831; ESP32_WROVER_SPARKFUN-IC-POWER_SOT23-5
PFMF.050.1: ESP32C6_VARISTORCN1812; ESP32C6_VARISTOR_CT/CN1812
Q1, Q2: 20V/4.2A/52mΩ/1.4W; ESP32_WROVER_SPARKFUN-DISCRETESEMI_SOT23-3
Q3: SI1308EDL-T1-GE3; SOT65P210X110-3N
R1, R1_BAT, R1_CL1, R1_PINH, R1_PINH1, R1_PWRUSB, R2, R2-PINH, R2-PINH1, R2-USB, R2-USB1, R2_BAT, R3, R4, R5, R6, R7, R8, R9, R10: ESP32_WROVER_EAGLE-LTSPICE_RR0402; ESP32_WROVER_EAGLE-LTSPICE_R0402
RESET_BUTTON: BUTTON_CUSYOMV1; MYBUTTON
R_BOOT: ESP32_WROVER_EAGLE-LTSPICE_RR0402; ESP32_WROVER_EAGLE-LTSPICE_R0402
R_CAPACITOR: ESP32_WROVER_EAGLE-LTSPICE_RR0402; ESP32_WROVER_EAGLE-LTSPICE_R0402
R_CHANGE: ESP32_WROVER_EAGLE-LTSPICE_RR0402; ESP32_WROVER_EAGLE-LTSPICE_R0402
R_RESET: ESP32_WROVER_EAGLE-LTSPICE_RR0402; ESP32_WROVER_EAGLE-LTSPICE_R0402
SENSOR2: ESP32_WROVER_BME680_BME680; ESP32_WROVER_BME680_PSON80P300X300X100-8N
SJ1: SJ
TP1, TP2, TP3, TP4, TP5, TP6, TP7, TP8, TP9, TP10, TP11, TP12, TP13, TP14, TP15, TP16, TP17: TPTP20R; TP20R
U1: W25Q512JVEIQ; SON127P600X800X80-9N
U2: ESP32-C6-WROOM-1-N8; XCVR_ESP32-C6-WROOM-1-N8
U3: DS3231SN#; SOIC127P1032X265-16N
U4: MAX17048G+T10; SON50P200X200X80-9N

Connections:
3V3: C9.1, D7.2 (ANODE), IC1.2 (VDD), J3.2, J4.P4 (VDD), Q2.3 (D), R1.1, R1_CL1.1, R1_PINH1.2, R2-PINH1.2, R5.2, R6.2, R7.2, R8.2, R9.2, R10.2, R_BOOT.1, R_CHANGE.1, R_RESET.1, TP16.TP, U1.3 (!WP!(IO2)), U1.7 (!HOLD!/!RESET!(IO3)), U1.8 (VCC), U2.2 (3V3), U3.2 (VCC)
4.7UF: C1_BAT2.2, C3.-, C4_USB.2, C5_USB.2
32KHZ: R2-PINH1.1, U2.9 (IO1), U3.1 (32KHZ)
100K: R1_PWRUSB.1
100UFTANT: C1_BAT2.1, C3.+, IC4.5 (VOUT)
DN: D1.4 (I/O2_2), J2.A7, J2.B7
DP: D1.6 (I/O1_2), J2.A6, J2.B6
EPD_3V3: C7.1, EPD_C5.1, J1.15, J1.16, L1.2, Q2.2 (S), TP17.TP
EPD_3V3_C: Q2.1 (G), R1_CL1.2, TP13.TP, U2.18 (IO20)
EPD_BUSY: J1.9, TP9.TP, U2.26 (IO3)
EPD_CS: D6.2, J1.12, R9.1, TP10.TP, U2.11 (IO10)
EPD_DC: J1.11, TP11.TP, U2.5 (IO5)
EPD_RST: J1.10, TP12.TP, U2.21 (IO23)
FLASH_CS: D9.2, R5.1, U1.1 (!CS), U2.12 (IO11)
GDR: J1.2, Q3.1 (G), R4.1
GND: BOOT_BUTTON.1, BOOT_BUTTON.2, C1.2, C1_BAT.2, C1_BAT1.2, C2.2, C2_BAT.2, C5.2, C6.2, C7.2, C8.2, C9.2, C10.2, CHANGE_BUTTON.1, CHANGE_BUTTON.2, CPH3225A.2, C_DELAY.2, D1.2 (GND), D3.1 (K), D6.1, D8.1, D9.1, D10.1, D11.1, D12.1, EPD_C1.2, EPD_C2.2, EPD_C5.2, EPD_C6.2, EPD_C7.2, EPD_C8.2, EPD_C9.2, EPD_C10.2, EPD_C11.2, EPD_C12.2, IC1.3 (GND), IC4.2 (VSS), J1.8, J1.17, J1.MP1, J1.MP2, J2.A12, J2.B1, J2.B12, J2.MP1, J2.MP2, J2.MP3, J2.MP4, J3.1, J4.G1 (GND_1), J4.G2 (GND_2), J4.G3 (GND_3), J4.G4 (GND_4), J4.P6 (VSS), MCP73831.2 (VSS), R2.1, R2-USB.2, R2_BAT.1, R4.2, RESET_BUTTON.1, RESET_BUTTON.2, SENSOR2.1 (GND), SENSOR2.5 (SDO), SENSOR2.7 (GND), SJ1.1, TP4.TP, TP5.TP, U1.4 (GND), U1.9 (EXP), U2.1 (GND), U2.28 (GND), U2.29_1 (GND), U2.29_2 (GND), U2.29_3 (GND), U2.29_4 (GND), U2.29_5 (GND), U2.29_6 (GND), U2.29_7 (GND), U2.29_8 (GND), U2.29_9 (GND), U3.13 (GND), U4.1 (CTG), U4.4 (GND), U4.6 (QSTRT), U4.9 (EP)
GPIO8: R1.2, U2.10 (IO8)
I2C_PW: C1.1, C2.1, R1_PINH.2, R2-PINH.2, SENSOR2.2 (CSB), SENSOR2.6 (VDDIO), SENSOR2.8 (VDD), U2.17 (IO19)
INT_RTC: R1_PINH1.1, TP15.TP, U2.8 (IO0), U3.3 (SQW/!INT)
IO/BOOT: BOOT_BUTTON.3, BOOT_BUTTON.4, C6.1, R_BOOT.2, U2.15 (IO9)
IO/CHANGE: C10.1, CHANGE_BUTTON.3, CHANGE_BUTTON.4, R_CHANGE.2, U2.23 (IO15)
MISO: D12.2, J4.P7 (DAT0), R8.1, TP6.TP, U1.2 (DO(IO1)), U2.27 (IO2)
MOSI: D11.2, J1.14, J4.P3 (CMD), R7.1, TP7.TP, U1.5 (DI(IO0)), U2.7 (IO7)
unnamed: J2.A5, R2-USB1.2
unnamed: J2.B5, R2-USB.1
unnamed: C4.1, D3.2 (A), D4.1 (K)
unnamed: MCP73831.1 (STAT), R1_BAT.1
unnamed: CHG_LED.C, R1_BAT.2
unnamed: MCP73831.5 (PROG), R2_BAT.2
unnamed: EPD_C12.1, J1.24
unnamed: EPD_C2.1, J1.5
unnamed: EPD_C10.1, J1.22
unnamed: C_DELAY.1, IC1.5 (CT)
unnamed: EPD_C8.1, J1.20
unnamed: EPD_C7.1, J1.19
unnamed: EPD_C6.1, J1.18
unnamed: EPD_C1.1, J1.4
unnamed: D7.1 (CATHODE), R_CAPACITOR.2
PREVGH: D5.1 (K), EPD_C9.1, J1.21
PREVGL: D4.2 (A), EPD_C11.1, J1.23
R2-USB1: R2-USB1.1
RESE: J1.3, Q3.2 (S), R3.1
RESE': R2.2, R3.2, SJ1.2
RESET: C5.1, IC1.1 (VOUT), RESET_BUTTON.3, RESET_BUTTON.4, R_RESET.2, U2.3 (EN)
RTC_RST: U2.16 (IO18), U3.4 (!RST)
RX: TP2.TP, U2.24 (RXD0/GPIO17)
SCA: J3.3
SCK: D10.2, J1.13, J4.P5 (CLK), R6.1, TP8.TP, U1.6 (CLK), U2.6 (IO6)
SCL: J3.4, R2-PINH.1, SENSOR2.4 (SCK), U2.20 (IO22), U3.16 (SCL), U4.7 (SCL)
SD0805S020S1R0: C1_BAT1.1, D2.1 (CATHODE), IC4.1 (VIN), IC4.3 (CE), Q1.2 (S)
SDA: R1_PINH.1, SENSOR2.3 (SDI), U2.19 (IO21), U3.15 (SDA), U4.8 (SDA)
SRC: C4.2, D5.2 (A), L1.1, Q3.3 (D)
SS_SD: D8.2, J4.P2 (CD/DAT3), R10.1, U2.4 (IO4)
TX: TP1.TP, U2.25 (TXD0/GPIO16)
USB_D+: D1.1 (I/O1_1), U2.14 (IO13)
USB_D-: D1.3 (I/O2_1), U2.13 (IO12)
VBAT: C2_BAT.1, MCP73831.3 (VBAT), Q1.3 (D), TP3.TP, U4.2 (CELL), U4.3 (VDD)
VBUS: C1_BAT.1, C4_USB.1, C5_USB.1, CHG_LED.A, D1.5 (VBUS), D2.2 (ANODE), MCP73831.4 (VIN), PFMF.050.1.2, Q1.1 (G), R1_PWRUSB.2, TP14.TP
VRTC: C8.1, CPH3225A.1, R_CAPACITOR.1, U3.14 (VBAT)
VUSB: J2.A4, J2.A9, J2.B4, J2.B9, PFMF.050.1.1

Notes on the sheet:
USB C connector & ESD protection
DMG2305UX-7
4.7uF
100K
100uF TANT
100nF
5k1
LDO Voltage Regulator
SD Card
2.2
Display Type Selector
10uF
68uH
4.7uF/25V
0.47
10K
E-Paper Drive Circuit
200
Li-Po Battery Charging Controller
10k
ESP32 C6
1uF/50V
0.1uF/50V
E-Paper Display Header
EPD Power
BME688
Environmental Sensor BME688
1uF
Voltage Supervisor + Reset & Boot / IO Button
Battery Charge Level
SD0805S020S1R0
C10_SUPERCAP
Test Pads
Qwiic / Stemma QT
SPI ESD Protection Lines
External NOR Flash 64MB

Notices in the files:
parts and their libraries:
COPYRIGHT: Copyright (C) 2024 Ultra Librarian. All rights reserved.
